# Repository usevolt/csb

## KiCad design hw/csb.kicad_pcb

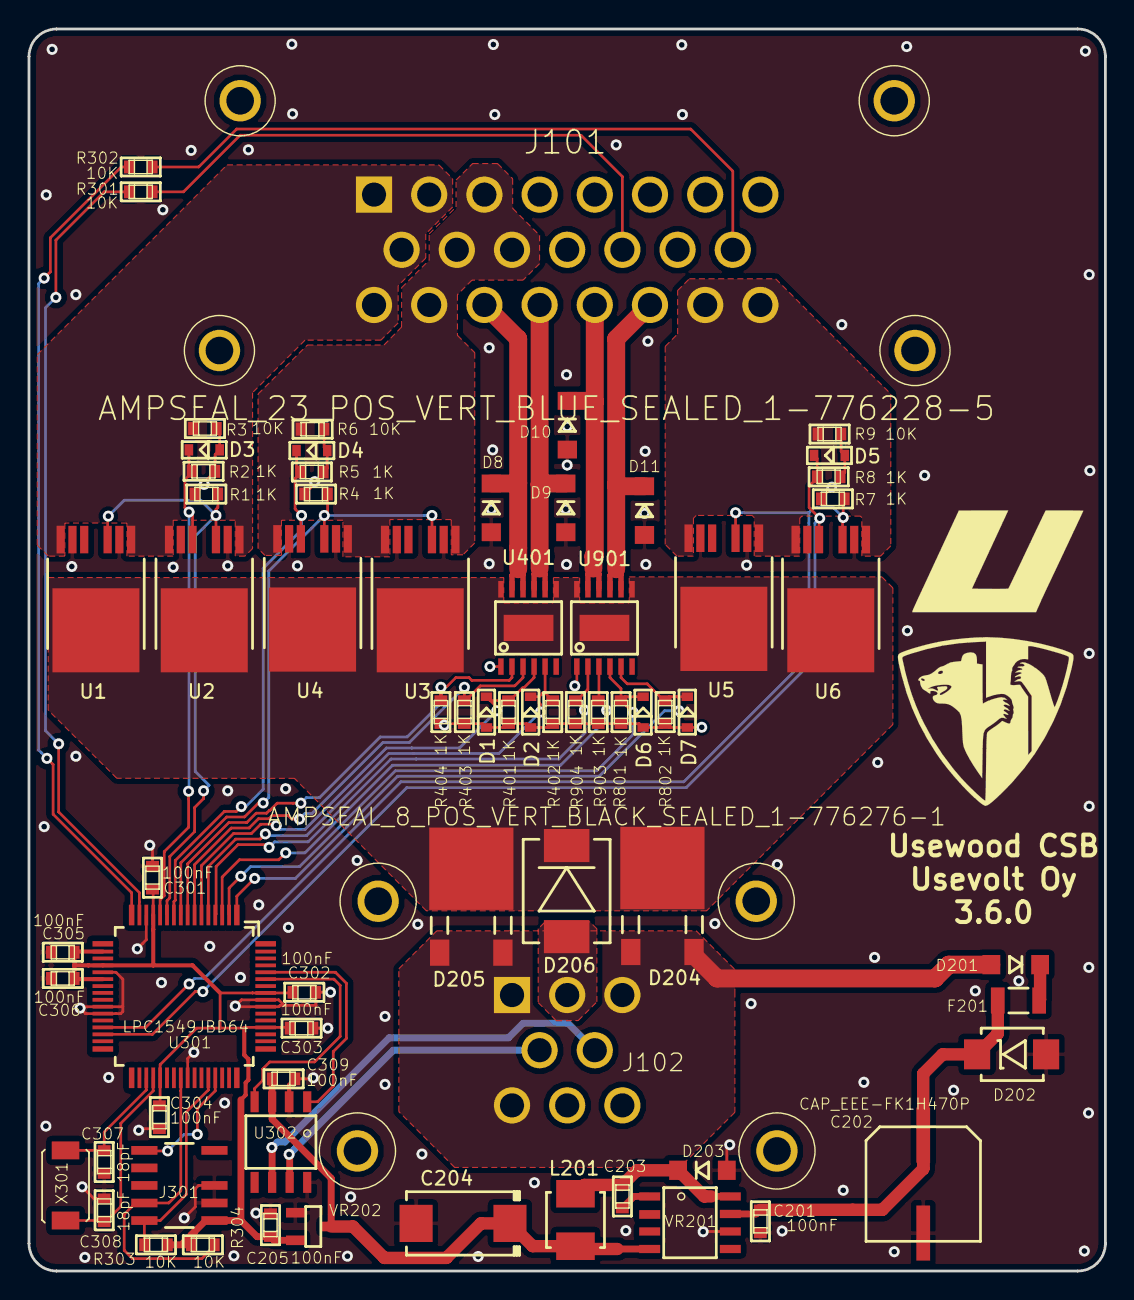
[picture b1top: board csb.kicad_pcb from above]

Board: 2 copper layers, 78.0 x 90.0 mm, 70 parts (0 on the bottom side), 43 nets.

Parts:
C201, C205, C301, C302, C303, C304, C305, C306, C309: 100nF; 0603
C202: CAP_EEE-FK1H470P
C203: 10nF; 0603
C204: T491D226K035AT; 7343
C307, C308: 18pF; 0603
D1, D2, D3, D4, D5, D6, D7: ZENER_MM3Z3V6T1G; SOD-323
D8, D9, D10, D11, D201, D203: DIODE_RS07J-GS18; DO219AB
D202: DIODE_TVS_SMBJ33A-TRDO-214AA; DO-214AA
D204, D205: SCHOTTKY_DIODE_V40PW10C; SlimDPAK
D206: DIODE_TVS_TPSMD28A; DO-214AB
F201: FUSE_MC36211_350MA; FUSE_MC36211
J101: AMPSEAL_23_POS_VERT_BLUE_SEALED_1-776228-5; AMPSEAL_23_POS_776200-1
J102: AMPSEAL_8_POS_VERT_BLACK_SEALED_1-776276-1; AMPSEAL_8_POS_776275-1
J301: ARM_JTAG_SWD_HEADER_10_PINSMD; ARM_10_PIN_JTAG_SWD_CONNECTOR
L201: IND_744045210
R1, R2, R4, R5, R7, R8, R401, R402, R403, R404, R801, R802, R903, R904: 1K; 0603
R3, R6, R9, R301, R302, R303, R304: 10K; 0603
U1, U2, U3, U4, U5, U6: VN5E010AH; HPAK
U301: LPC1549JBD64; QFP64
U302: MCP2551_SOIC8; SOIC8
U401, U901: VND5050AJTR-E; PowerSSO-12
VR201: LM2671SOIC8; SOIC8
VR202: REG_MCP1700; SOT-23_3-PIN
X301: XTAL_7A-12.000MAAJ-T; XTAL_7A-20.000MAJ

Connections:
+3V3: C205.1, C301.1, C302.1, C303.1, C304.1, C305.1, C306.1, J301.P$1, R303.2, R304.2, U301.P$13, U301.P$18, U301.P$20, U301.P$22, U301.P$37, U301.P$52, U301.P$57, VR202.2
+5V: C204.+, C309.1, L201.2, U302.3, VR201.4, VR202.3
/BACK_4A: D9.P$2, J101.P$19, U401.8, U401.9
/BEACON_4A: D8.P$2, J101.P$18, U401.10, U401.11
/CANH: J102.P$4, U302.7
/CANL: J102.P$5, U302.6
/COOLER_30A: J101.P$22, J101.P$23, R9.2, U5.1, U5.7, U6.1, U6.7
/DRIVE_15A: J101.P$1, J101.P$2, J101.P$9, J101.P$16, R3.2, U1.1, U1.7, U2.1, U2.7
/IN_4A: D10.P$2, J101.P$20, U901.10, U901.11
/LPC1549/BACK: R403.2, U301.P$7, U401.3
/LPC1549/BACK_SENSE: D1.1, R401.1, U301.P$6, U401.4
/LPC1549/BEACON: R404.2, U301.P$8, U401.2
/LPC1549/BEACON_SENSE: D2.1, R402.1, U301.P$5, U401.5
/LPC1549/CAN_RX: U301.P$59, U302.4
/LPC1549/CAN_TX: U301.P$60, U302.1
/LPC1549/COOLER: R7.2, U5.3, U6.3, U301.P$29
/LPC1549/COOLER_P: J101.P$15, R302.1
/LPC1549/COOLER_SENSE: D5.1, R8.1, U6.5, U301.P$30
/LPC1549/DRIVE: R1.2, U1.3, U2.3, U301.P$11
/LPC1549/DRIVE_SENSE: D3.1, R2.1, U2.5, U301.P$12
/LPC1549/IN: R904.2, U301.P$4, U901.2
/LPC1549/IN_SENSE: D7.1, R802.1, U301.P$1, U901.5
/LPC1549/RESET: J301.P$9, U301.P$45
/LPC1549/WIPER_POS: J101.P$13, R301.1
/Power Supply/VIN: D201.P$1, D204.1, D204.2, D205.1, D205.2, J102.P$1, J102.P$3, J102.P$6
/Sheet5A02A41E/IN1: R903.2, U301.P$3, U901.3
/Sheet5A02A41E/SENSE1: D6.1, R801.1, U301.P$2, U901.4
/Sheet5A019745/IN1: R4.2, U3.3, U4.3, U301.P$9
/Sheet5A019745/SENSE1: D4.1, R5.1, U4.5, U301.P$10
/WIPER_4A: D11.P$2, J101.P$21, U901.8, U901.9
/WORK_15A: J101.P$3, J101.P$10, J101.P$11, J101.P$17, R6.2, U3.1, U3.7, U4.1, U4.7
GND: C201.2, C202.-, C204.-, C205.2, C301.2, C302.2, C303.2, C304.2, C305.2, C306.2, C307.2, C308.2, C309.2, D1.2, D2.2, D3.2, D4.2, D5.2, D6.2, D7.2, D8.P$1, D9.P$1, D10.P$1, D11.P$1, D202.P$1, D203.P$1, D206.1, J102.P$2, J301.P$3, J301.P$5, R1.1, R2.2, R3.1, R4.1, R5.2, R6.1, R7.1, R8.2, R9.1, R401.2, R402.2, R403.1, R404.1, R801.2, R802.2, R903.1, R904.1, U1.2, U1.6, U2.2, U2.6, U3.2, U3.6, U4.2, U4.6, U5.2, U5.6, U6.2, U6.6, U301.P$14, U301.P$21, U301.P$26, U301.P$27, U301.P$41, U301.P$55, U301.P$56, U302.2, U302.8, U401.1, U901.1, VR201.6, VR202.1
unnamed: C201.1, C202.+, D202.P$2, F201.P$2, VR201.7
unnamed: C203.1, VR201.1
unnamed: C203.2, D203.P$2, L201.1, VR201.8
unnamed: C307.1, U301.P$35, X301.P$1
unnamed: C308.1, U301.P$36, X301.P$2
unnamed: D201.P$2, F201.P$1
unnamed: J301.P$2, R303.1, U301.P$44
unnamed: J301.P$4, R304.1, U301.P$40
unnamed: R301.2, U301.P$15
unnamed: R302.2, U301.P$16
VDD: D204.3, D205.3, D206.2, U1.4, U2.4, U3.4, U4.4, U5.4, U6.4, U401.7, U401.12, U401.13, U901.7, U901.12, U901.13

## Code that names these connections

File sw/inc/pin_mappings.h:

/*
 * pin_mappings.h
 *
 *  Created on: Jan 27, 2015
 *      Author: usenius
 *
 *  Defines keypad pin mappings for different pcb revisions used
 */

#ifndef UW_MB_SRC_PIN_MAPPINGS_H_
#define UW_MB_SRC_PIN_MAPPINGS_H_

#include <uv_gpio.h>
#include <uv_timer.h>
#include <uv_adc.h>


#define BACK_LIGHT_SENSE_CHN		ADC0_6
#define WORK_LIGHT_SENSE_CHN		ADC0_2
#define BEACON_SENSE_CHN			ADC0_7
#define IN_LIGHT_SENSE_CHN			ADC0_11
#define DRIVE_LIGHT_SENSE_CHN		ADC0_0
#define COOLER_SENSE_CHN			ADC1_7
#define WIPER_SENSE_CHN				ADC0_10

#define WORK_LIGHT_IO				P0_5
#define BACK_LIGHT_IO				P0_3
#define BEACON_IO					P0_4
#define IN_LIGHT_IO					P1_0
#define DRIVE_LIGHT_IO				P0_7
#define WIPER_IO					P0_31
#define WIPER_SENSOR_IO				P1_1
#define COOLER_IO					P0_13
#define COOLER_P_IO					P0_9





#endif /* UW_MB_SRC_PIN_MAPPINGS_H_ */

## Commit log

2017-06-28 Started designing CSB board
2017-07-03 first pcb revision ready to order
2017-08-03 sw directory created, oil cooler added in hw
2017-08-11 ready for testing in real machine for first time
2017-08-14 revision 2.0.0 pcb ready to order
2017-08-28 removing release directory from version control
2017-08-28 output moving averaging removed and step cycle set to 1 ms
2017-08-30 testing with different step cycles
2017-09-05 at least shortcirucuit protection works
2017-10-19 starting to draw version 4.0.0
2017-10-19 all outputs tested with multimeter, wiper logic still missing
2017-10-24 wiper logic implemented, not tested
2017-10-26 wiper speed removed from txpdo
2017-11-02 implementing sw, wiper not yet working
2017-11-03 first working revision with FSB & ESB
2017-11-03 added .gitmodules file
2017-11-16 3.1.0 hw created, not yet ordered
2017-11-18 3.1.0 gerber created for seeed studios
2017-11-20 oil cooler removed, 3.2.0 ready to order
2017-12-17 oil cooler moved to ESB
2017-12-19 hw 3.3 created
2017-12-19 hw 3.3.0 ordered from seeed
2018-02-05 working revision FM_6.6.1
2018-02-16 small modifications to debug messages
2018-03-12 CSB_WIPER_SPEED added to TXPDO1
2018-03-26 wiper request implemented
2018-04-07 wiper 1 time wiping bug fix
2018-04-14 wiper home polarity implemented
2018-06-05 cooler max current set to 30A
2018-08-15 making modifications to pcb...
2018-09-09 bug fix: back light is controlled by drive ligths
2018-09-18 cooler and wiper is stopper if ignkey is off for too long
2018-09-18 fsb seat switch obj dict entry added
2018-10-14 Drawing pcb 4.0.0
2018-11-13 wiper is controlled with keypad
2018-11-27 work & drive light max current increased to 20 A
2018-11-28 pcb 3.4.0 created, ready for order
2018-12-07 uv_hal updated to latest CONFIG_CANOPEN_AUTO_PREOPERATIONAL settings
2018-12-19 191218: csb bootloader updated and ligth max current increased to 20A
2018-12-21 3.4.0 gerber files generated
2019-01-02 CM_6.2.3 released
2019-01-21 pin mappings updated for hw 3.4.0
2019-01-29 CAP moved away from AMPSEAL leg
2019-01-29 pcb 3.5.0 created, added protection diodes for vnd4040 outputs
2019-01-29 silkscreen updated for 3.5.0
2019-02-10 090219: wiper speed set acording to Tammekivi wishes:
    wiper interval is set by pressing the button twice and measuring the time between the presses
2019-02-10 pcb 3.6.0 created, with double fets in work & drive lights
2019-02-25 vnd5050 current amp multiplier updated for 1k resistors
2019-03-14 HAL update for small bugfixes
2019-03-16 new mode for wiper (from tammekivi) delay based button pressing
2019-03-16 wiper traditional mode made default
2019-10-09 submodule urls set to https github
2020-08-04 040820: wiper speed logic interval delay lengthened
2021-01-04 work & drive lights turn off when starting
